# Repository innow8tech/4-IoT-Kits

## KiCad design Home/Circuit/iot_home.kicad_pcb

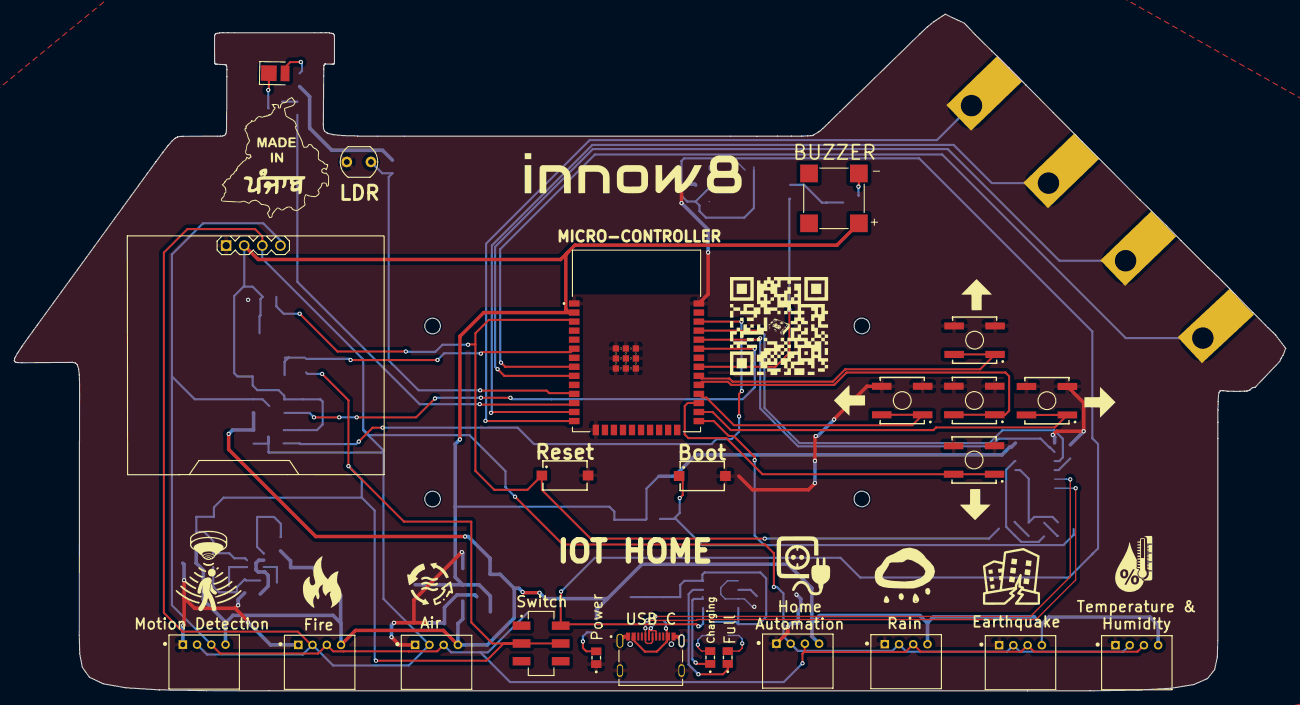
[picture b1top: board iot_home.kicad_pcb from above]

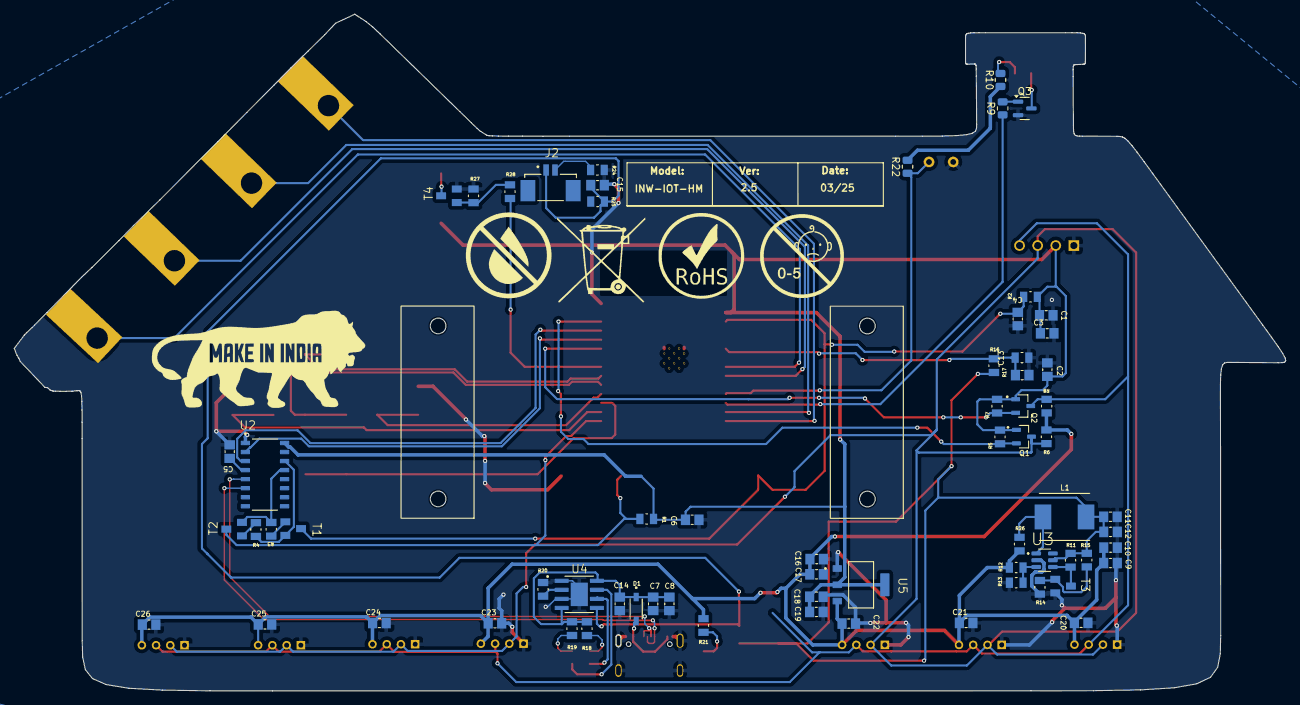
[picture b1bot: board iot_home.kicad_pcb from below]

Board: 2 copper layers, 178.6 x 95.0 mm, 97 parts (69 on the bottom side), 52 nets.

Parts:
C1, C7, C10, C12, C13, C16, C19: 47uF; CAPC2012X135N
C2, C3, C4, C5, C6, C8, C11, C14, C15, C17, C18, C20, C21, C22, C23, C24, C25, C26: 100nF; CAPC2012X135N
C9: 100uF; CAPC2012X135N
D1: 1N5819HW-7-F; SOD3715X145N
D3: LED; LED_PLCC_2835
D5: green; LEDC2012X70N
D6: red; LEDC2012X70N
D7: white; LEDC2012X70N
J1: CSP-USC16-TR; VALCON_CSP-USC16-TR
J2: 10114828-13102LF; AMPHENOL_10114828-13102LF
J3, J4, J5, J6, J7, J8, J9: S4B-PH-K-S(LF)(SN); JST_S4B-PH-K-S(LF)(SN)
J10, J11, J12, J13: Conn_01x01_Pin; educate_touchpad
L1: ASPI-0630LR-5R6M-T15; IND_ASPI-0630LR-5R6M-T15
LS1: CMT-8530S-SMT; CUI_CMT-8530S-SMT
Q1, Q2: BSS138; SOT95P240X111-3N
Q3: BC847; SOT-23
R1, R2, R15, R27, R28: 1k; RESC2012X65N
R3, R4, R5, R6, R7, R8, R11, R14, R18, R19, R21: 10k; RESC2012X65N
R9, R22: 1k; R_0805_2012Metric
R10: 100; R_0805_2012Metric
R12: 15k; RESC2012X65N
R13: 2k; RESC2012X65N
R16, R17: 47k; RESC2012X65N
R20: 3k; RESC2012X65N
R23: LDR07; R_LDR_5.1x4.3mm_P3.4mm_Vertical
R24, R25, R26: 0; RESC2012X65N
S1: boot; 434121025816
S2: reset; 434121025816
S3: JS202011SCQN; SW_JS202011SCQN
S8, S9, S10, S11, S12: B3SL-1022P; SW_B3SL-1022P
SV1: MA04-1; DISPLAY-OLED-128X64-I2C
T1, T2, T3, T4: BC847; SOT23
U1: ESP32-WROOM-32E_(4MB); XCVR_ESP32-WROOM-32E_(4MB)
U2: CH340C; SOIC127P600X180-16N
U3: MT3608; SOT95P280X145-6N
U4: TP4056; SOP127P600X175-9N
U5: AMS1117-3.3; SOT229P700X180-4N
edukit_mountinghole3, edukit_mountinghole3#2: edukit_mountinghole

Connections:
+3V3: R10.2, R22.2
/3V3: C1.1, C2.1, C3.1, C6.1, C18.1, C19.1, LS1.P, Q1.1 (G), Q2.1 (G), R1.2, R2.2, R5.2, R7.2, SV1.2, U1.2 (3V3), U2.16 (VCC), U5.2 (VOUT)
/5V: C9.1, C10.1, C16.1, C17.1, C20.1, C21.1, C22.1, C23.1, C24.1, C25.1, C26.1, J3.4, J4.4, J5.4, J6.4, J7.4, J8.4, J9.4, R6.2, R8.2, R12.2, R21.2, R26.1, U5.3 (VIN)
/5V_CHG: D1.A, J1.A4 (VBUS_A), J1.A9 (VBUS_A), J1.B9 (VBUS_B)
/5V_OUT: C7.1, C8.1, C14.1, D1.C (K), R18.2, R19.2, U4.4 (VCC), U4.8 (CE)
/B+: C15.2, J2.1, R25.2, S3.4, U4.5 (BAT)
/B+_OUT: C11.1, C12.1, L1.1, R11.2, R15.2, R16.1, S3.2, S3.5, U3.5 (IN)
/B-: J2.2, R24.1
/BATT_GAUGE: C13.1, R16.2, R17.2, U1.6 (IO34)
/BOOT_0: R1.1, S1.1, T2.3 (C), U1.25 (IO0)
/BUZZER: R28.2, U1.31 (IO19)
/CONTROLLER_SCL: Q1.2 (S), R5.1, U1.36 (IO22)
/CONTROLLER_SDA: Q2.2 (S), R7.1, U1.33 (IO21)
/DA+: J1.A6 (DP1), J1.B6 (DP2), U2.5 (UD+)
/DA-: J1.A7 (DN1), J1.B7 (DN2), U2.6 (UD-)
/ESP_EN: C4.1, R2.1, S2.1, T1.3 (C), U1.3 (EN)
/LDR: R22.1, R23.1, U1.11 (IO26)
/RGB_DIN: R9.1, U1.12 (IO27)
/RXD: U1.34 (RXD0), U2.2 (TXD)
/SCL: J3.2, J4.2, J5.2, J6.2, J7.2, J8.2, J9.2, Q1.3 (D), R6.1, SV1.3
/SDA: J3.3, J4.3, J5.3, J6.3, J7.3, J8.3, J9.3, Q2.3 (D), R8.1, SV1.4
/SW_CENTER: S12.1, S12.2, U1.29 (IO5)
/SW_DOWN: S11.1, S11.2, U1.27 (IO16)
/SW_LEFT: S10.1, S10.2, U1.28 (IO17)
/SW_RIGHT: S8.1, S8.2, U1.26 (IO4)
/SW_UP: S9.1, S9.2, U1.30 (IO18)
/TOUCH_PAD_1: J10.1, U1.8 (IO32)
/TOUCH_PAD_2: J11.1, U1.9 (IO33)
/TOUCH_PAD_3: J12.1, U1.13 (IO14)
/TOUCH_PAD_4: J13.1, U1.14 (IO12)
/TXD: U1.35 (TXD0), U2.3 (RXD)
GND: C1.2, C2.2, C3.2, C4.2, C5.1, C6.2, C7.2, C8.2, C9.2, C10.2, C11.2, C12.2, C13.2, C14.2, C15.1, C16.2, C17.2, C18.2, C19.2, C20.2, C21.2, C22.2, C23.2, C24.2, C25.2, C26.2, D7.C, J1.A1 (GND_A), J1.B1 (GND_B), J1.S1 (SHELL_GND), J1.S3 (SHELL_GND), J1.S4 (SHELL_GND), J3.1, J4.1, J5.1, J6.1, J7.1, J8.1, J9.1, Q3.2 (E), R13.1, R14.1, R17.1, R20.1, R23.2, R24.2, R27.1, S1.2, S2.2, S8.3, S8.4, S9.3, S9.4, S10.3, S10.4, S11.3, S11.4, S12.3, S12.4, SV1.1, T3.2 (E), T4.2 (E), U1.1 (GND), U1.15 (GND), U1.38 (GND), U1.39_1 (GND), U1.39_2 (GND), U1.39_3 (GND), U1.39_4 (GND), U1.39_5 (GND), U1.39_6 (GND), U1.39_7 (GND), U1.39_8 (GND), U1.39_9 (GND), U2.1 (GND), U3.2 (GND), U4.1 (TEMP), U4.3 (GND), U4.9 (EP), U5.1 (GND/ADJ)
unnamed: D3.2 (A), R10.1
unnamed: D3.1 (K), Q3.3 (C)
unnamed: D5.A, R18.1
unnamed: D6.A, R19.1
unnamed: D7.A, R21.1
unnamed: Q3.1 (B), R9.2
unnamed: R3.2, T1.1 (B)
unnamed: R4.1, T1.2 (E), U2.14 (~RTS)
unnamed: R4.2, T2.1 (B)
unnamed: R3.1, T2.2 (E), U2.13 (~DTR)
unnamed: R14.2, R15.1, T3.1 (B)
unnamed: R11.1, T3.3 (C), U3.4 (EN)
unnamed: R27.2, R28.1, T4.1 (B)
unnamed: LS1.N, T4.3 (C)
unnamed: C5.2, U2.4 (V3)
unnamed: R12.1, R13.2, U3.3 (FB)
unnamed: L1.2, R26.2, U3.1 (SW)
unnamed: R20.2, U4.2 (PROG)
unnamed: D6.C, U4.7 (~CHRG)
unnamed: D5.C, U4.6 (~STDBY)

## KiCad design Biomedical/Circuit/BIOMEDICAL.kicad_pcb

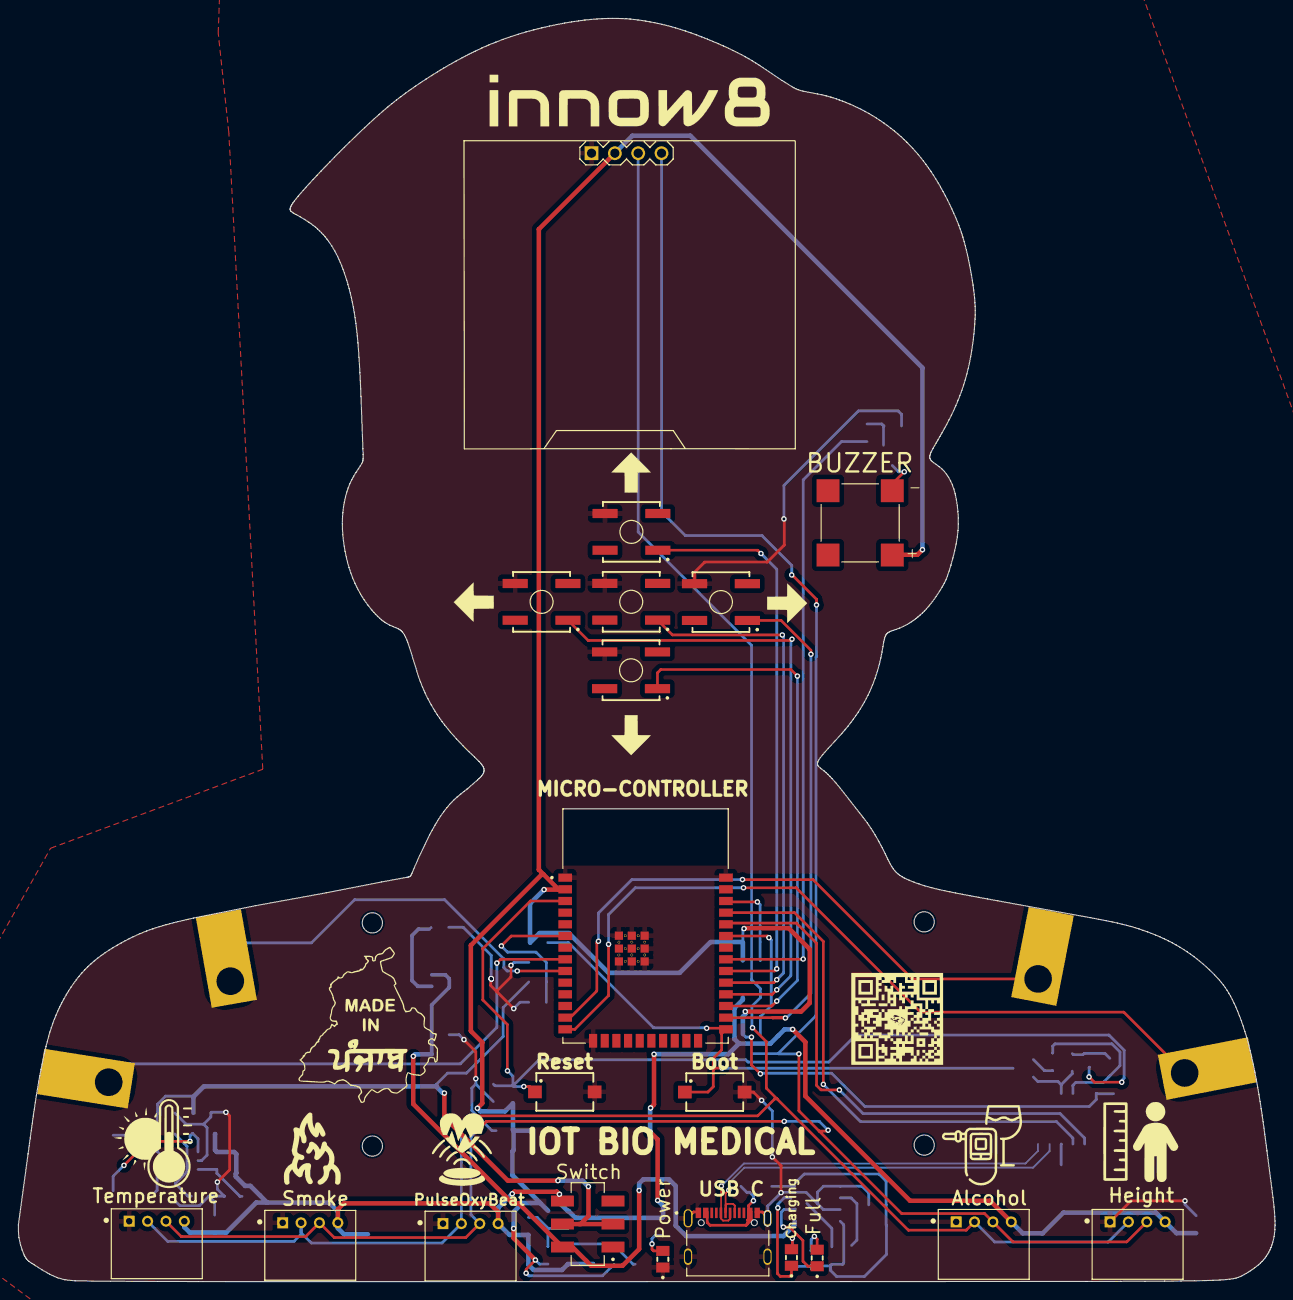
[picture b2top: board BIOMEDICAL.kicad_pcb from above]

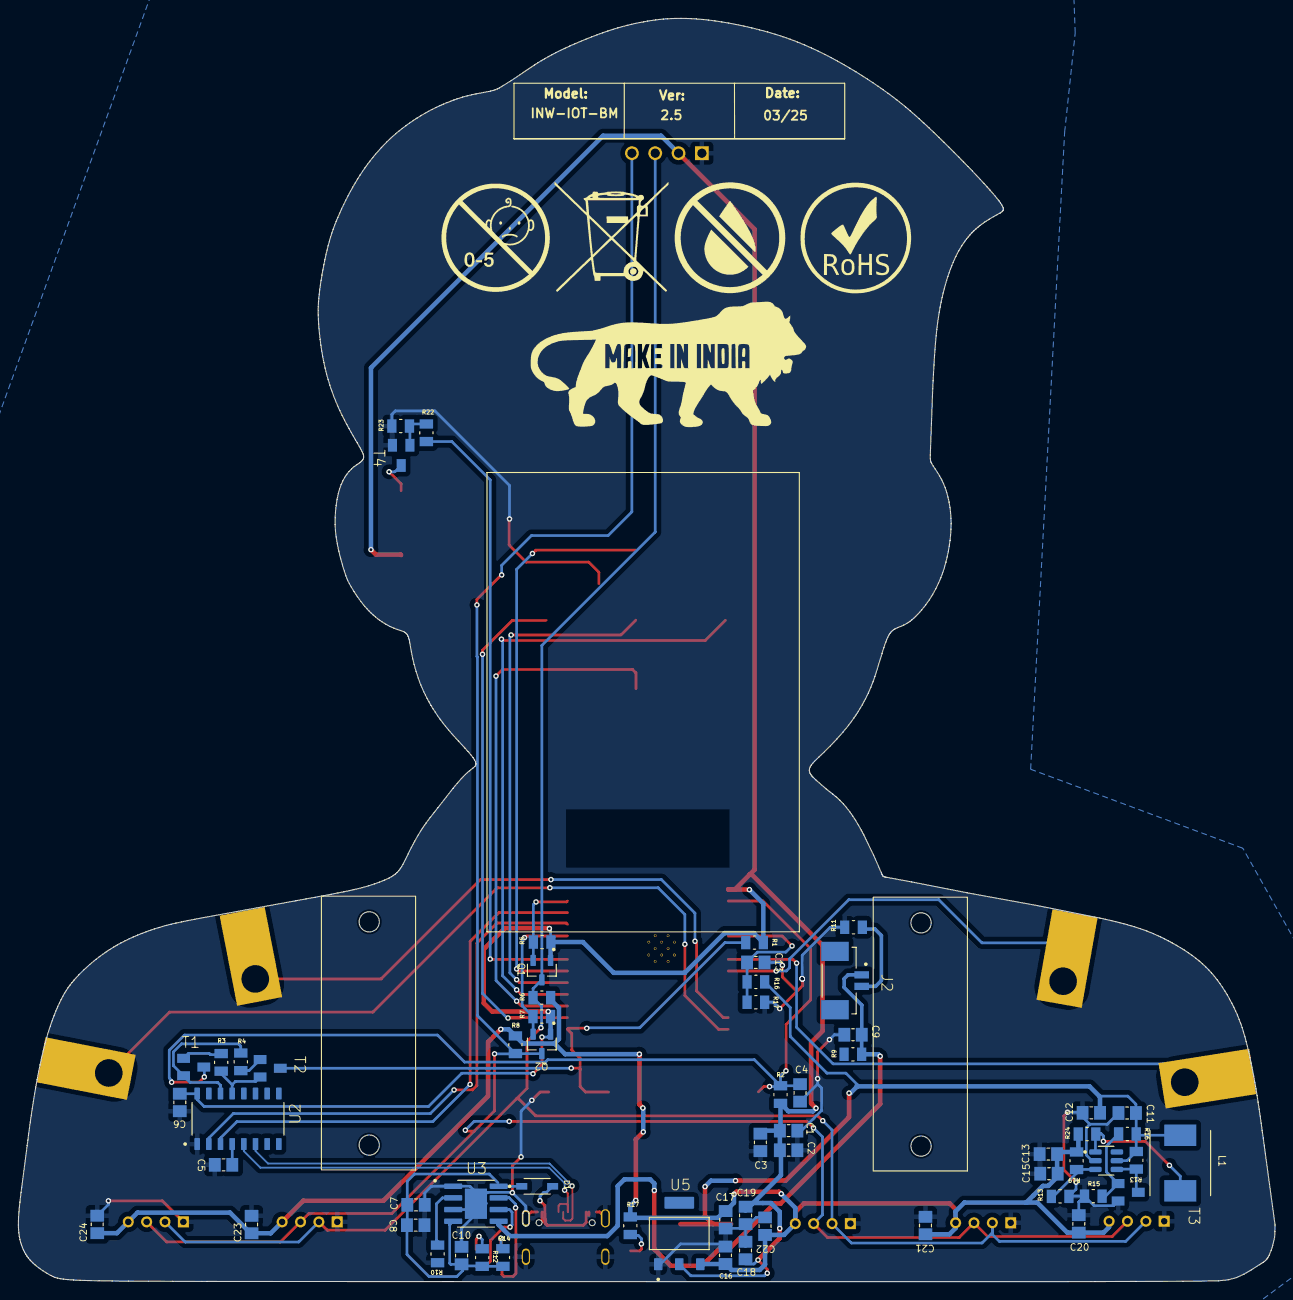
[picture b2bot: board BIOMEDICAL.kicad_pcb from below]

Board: 2 copper layers, 136.8 x 137.5 mm, 87 parts (63 on the bottom side), 46 nets.

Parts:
C1, C4, C5, C6, C8, C9, C10, C12, C15, C16, C17, C20, C21, C22, C23, C24: 100nF; CAPC2012X135N
C2, C7, C11, C13, C18, C19: 47uF; CAPC2012X135N
C3: 10uF; CAPC2012X135N
C13#2: GCM21BR71H104KA37K; CAPC2012X135N
D1: 1N5819HW-7-F; SOD3715X145N
D2: GREEN; LEDC2012X70N
D3: RED; LEDC2012X70N
D4: white; LEDC2012X70N
J1: CSP-USC16-TR; VALCON_CSP-USC16-TR
J2: 10114828-13102LF; AMPHENOL_10114828-13102LF
J3, J4, J5, J6, J7: S4B-PH-K-S(LF)(SN); JST_S4B-PH-K-S(LF)(SN)
J8, J9, J10, J11: Conn_01x01_Pin; educate_touchpad
L1: ASPI-0630LR-5R6M-T15; IND_ASPI-0630LR-5R6M-T15
LS1: CMT-8530S-SMT; CUI_CMT-8530S-SMT
Q1, Q2: BSS138; SOT95P240X111-3N
R1: 1K; RESC2012X65N
R2, R13, R13#2, R22, R23: 1k; RESC2012X65N
R3, R4, R5, R6, R7, R8, R12, R14, R15, R16, R16#2, R17: 10k; RESC2012X65N
R9, R11, R24: 0; RESC2012X65N
R10: 3k; RESC2012X65N
R17#2: RP73PF2A33K2BTDF; RESC2012X65N
R19: 2k; RESC2012X65N
S1: Boot; 434121025816
S2: Reset; 434121025816
S3: JS202011SCQN; SW_JS202011SCQN
S8, S9, S10, S11, S12: B3SL-1022P; SW_B3SL-1022P
SV1: MA04-1; DISPLAY-OLED-128X64-I2C
T1, T2, T3, T4: BC847; SOT23
U1: ESP32-WROOM-32E_(4MB); XCVR_ESP32-WROOM-32E_(4MB)
U2: CH340C; SOIC127P600X180-16N
U3: TP4056; SOP127P600X175-9N
U4: MT3608; SOT95P280X145-6N
U5: AMS1117-3.3; SOT229P700X180-4N
edukit_mountinghole3, edukit_mountinghole3#2: edukit_mountinghole

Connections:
/3V3: C1.1, C2.1, C3.1, C6.1, C18.1, C19.1, LS1.P, Q1.1 (G), Q2.1 (G), R1.2, R2.2, R5.2, R7.2, SV1.2, U1.2 (3V3), U2.16 (VCC), U5.2 (VOUT)
/5V: C13.1, C15.1, C16.1, C17.1, C20.1, C21.1, C22.1, C23.1, C24.1, J3.4, J4.4, J5.4, J6.4, J7.4, R6.2, R8.2, R17.2, R19.2, R24.1, U5.3 (VIN)
/5V_CHG: D1.A, J1.A4 (VBUS_A), J1.A9 (VBUS_A), J1.B4 (VBUS_B), J1.B9 (VBUS_B)
/5V_OUT: C7.1, C8.1, C10.1, D1.C (K), R12.2, R14.2, U3.4 (VCC), U3.8 (CE)
/B+: C9.2, J2.1, R9.2, S3.4, U3.5 (BAT)
/B+_OUT: C11.1, C12.1, L1.1, R13.2, R16.2, R16#2.1, S3.2, S3.5, U4.5 (IN)
/B-: J2.2, R11.1
/BATT_GAUGE: C13#2.1, R16#2.2, R17#2.2, U1.6 (IO34)
/BOOT_0: R1.1, S1.1, T2.3 (C), U1.25 (IO0)
/BUZZER: R22.2, U1.31 (IO19)
/CONTROLLER_SCL: Q1.2 (S), R5.1, U1.36 (IO22)
/CONTROLLER_SDA: Q2.2 (S), R7.1, U1.33 (IO21)
/DA+: J1.A6 (DP1), J1.B6 (DP2), U2.5 (UD+)
/DA-: J1.A7 (DN1), J1.B7 (DN2), U2.6 (UD-)
/ESP_EN: C4.1, R2.1, S2.1, T1.3 (C), U1.3 (EN)
/GND: C1.2, C2.2, C3.2, C4.2, C5.1, C6.2, C7.2, C8.2, C9.1, C10.2, C11.2, C12.2, C13.2, C13#2.2, C15.2, C16.2, C17.2, C18.2, C19.2, C20.2, C21.2, C22.2, C23.2, C24.2, D4.C, J1.A1 (GND_A), J1.A12 (GND_A), J1.B1 (GND_B), J1.B12 (GND_B), J1.S1 (SHELL_GND), J1.S3 (SHELL_GND), J1.S4 (SHELL_GND), J3.1, J4.1, J5.1, J6.1, J7.1, R10.1, R11.2, R13#2.1, R15.1, R17#2.1, R23.1, S1.2, S2.2, S8.4, S9.4, S10.4, S11.4, S12.4, SV1.1, T3.2 (E), T4.2 (E), U1.1 (GND), U1.15 (GND), U1.38 (GND), U1.39_1 (GND), U1.39_2 (GND), U1.39_3 (GND), U1.39_4 (GND), U1.39_5 (GND), U1.39_6 (GND), U1.39_7 (GND), U1.39_8 (GND), U1.39_9 (GND), U2.1 (GND), U3.1 (TEMP), U3.3 (GND), U3.9 (EP), U4.2 (GND), U5.1 (GND/ADJ)
/RXD: U1.34 (RXD0), U2.2 (TXD)
/SCL: J3.2, J4.2, J5.2, J6.2, J7.2, Q1.3 (D), R6.1, SV1.3
/SDA: J3.3, J4.3, J5.3, J6.3, J7.3, Q2.3 (D), R8.1, SV1.4
/SW_CENTER: S12.1, U1.29 (IO5)
/SW_DOWN: S11.1, U1.27 (IO16)
/SW_LEFT: S10.1, U1.28 (IO17)
/SW_RIGHT: S8.1, U1.26 (IO4)
/SW_UP: S9.1, U1.30 (IO18)
/TOUCH_PAD_1: J8.1, U1.8 (IO32)
/TOUCH_PAD_2: J9.1, U1.9 (IO33)
/TOUCH_PAD_3: J10.1, U1.13 (IO14)
/TOUCH_PAD_4: J11.1, U1.14 (IO12)
/TXD: U1.35 (TXD0), U2.3 (RXD)
unnamed: D2.A, R12.1
unnamed: D3.A, R14.1
unnamed: D4.A, R17.1
unnamed: R3.2, T1.1 (B)
unnamed: R4.1, T1.2 (E), U2.14 (~RTS)
unnamed: R4.2, T2.1 (B)
unnamed: R3.1, T2.2 (E), U2.13 (~DTR)
unnamed: R15.2, R16.1, T3.1 (B)
unnamed: R13.1, T3.3 (C), U4.4 (EN)
unnamed: R22.1, R23.2, T4.1 (B)
unnamed: LS1.N, T4.3 (C)
unnamed: C5.2, U2.4 (V3)
unnamed: R13#2.2, R19.1, U4.3 (FB)
unnamed: L1.2, R24.2, U4.1 (SW)
unnamed: R10.2, U3.2 (PROG)
unnamed: D3.C, U3.7 (~CHRG)
unnamed: D2.C, U3.6 (~STDBY)

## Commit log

2025-03-05 Create demo
2025-03-05 Create Production Files
2025-03-05 Create d
2025-03-05 Create Production File
2025-03-05 Create ab
2025-03-05 Create abc
